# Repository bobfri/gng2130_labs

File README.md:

# gng2130_labs
lab finished matterials
pcb desing
mfs switch libary
schematic
board

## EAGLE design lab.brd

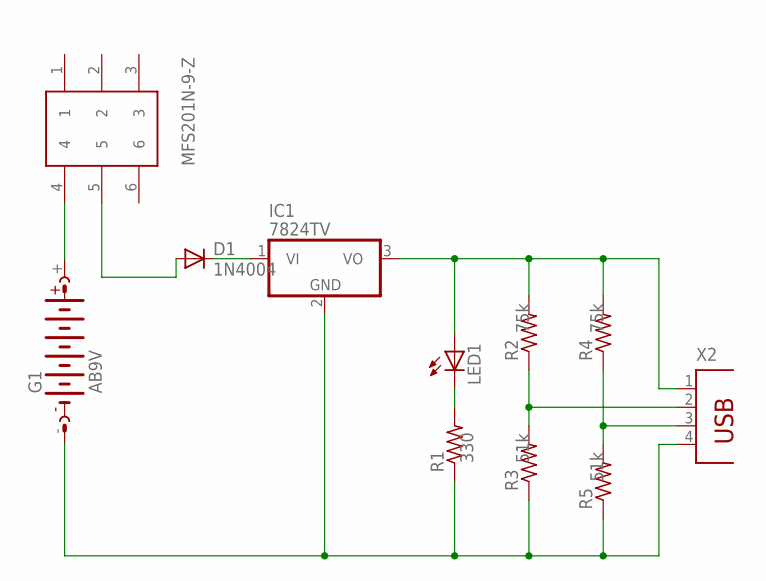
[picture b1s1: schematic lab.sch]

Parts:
D1: 1N4004; DO41-10
G1: AB9V
IC1: 7824TV; TO220V
LED1: LED5MM
R1, R2, R3, R4, R5: R-US_0207/10; 0207/10
U$1: MFS201N-9-Z
X2: PN87520

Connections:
unnamed: G1.+, U$1.4
unnamed: G1.-, IC1.2 (GND), R1.1, R3.1, R5.1, X2.4
unnamed: D1.A, U$1.5
unnamed: D1.C, IC1.1 (VI)
unnamed: IC1.3 (VO), LED1.A, R2.2, R4.2, X2.1
unnamed: R2.1, R3.2, X2.2
unnamed: R4.1, R5.2, X2.3
unnamed: LED1.K (C), R1.2

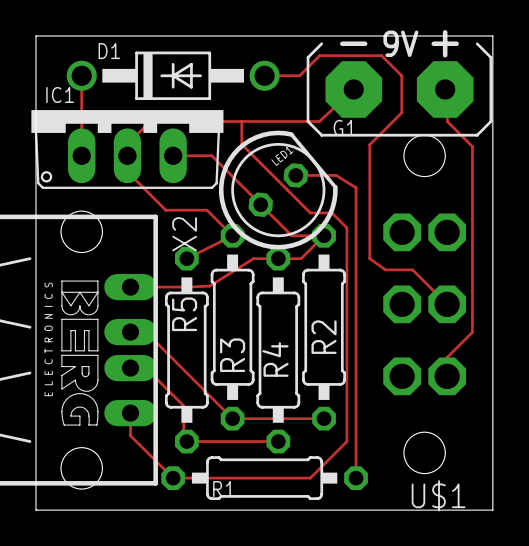
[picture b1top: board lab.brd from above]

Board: 2 copper layers, 25.4 x 26.3 mm, 11 parts (0 on the bottom side), 8 nets.

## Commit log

2018-10-17 Set theme jekyll-theme-cayman
